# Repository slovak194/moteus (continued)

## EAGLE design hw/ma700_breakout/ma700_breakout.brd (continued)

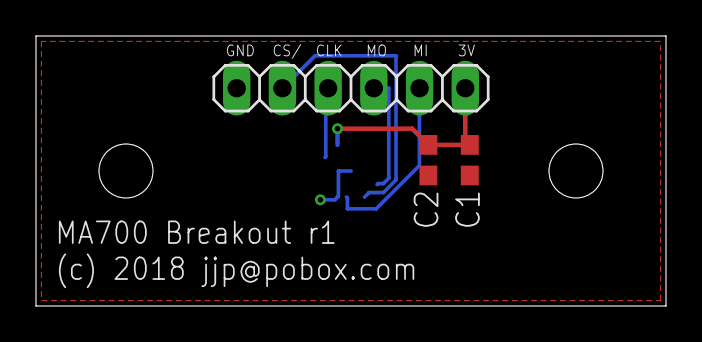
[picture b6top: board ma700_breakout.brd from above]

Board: 2 copper layers, 35.0 x 15.0 mm, 4 parts (1 on the bottom side), 6 nets.

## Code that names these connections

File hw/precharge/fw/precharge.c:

// Copyright 2019 Josh Pieper, jjp@pobox.com.
//
// Licensed under the Apache License, Version 2.0 (the "License");
// you may not use this file except in compliance with the License.
// You may obtain a copy of the License at
//
//     http://www.apache.org/licenses/LICENSE-2.0
//
// Unless required by applicable law or agreed to in writing, software
// distributed under the License is distributed on an "AS IS" BASIS,
// WITHOUT WARRANTIES OR CONDITIONS OF ANY KIND, either express or implied.
// See the License for the specific language governing permissions and
// limitations under the License.

#include <avr/cpufunc.h>
#include <avr/interrupt.h>
#include <avr/io.h>
#include <util/delay.h>

//                 --------------
//               --|VCC      GND|--
//    FET_MAIN   --|PB0      PA0|-- VSAMP_IN
//    FET_PCHG   --|PB1      PA1|-- VSAMP_OUT
//       RESET   --|PB3      PA2|-- LED1
//               --|PB2      PA3|-- LED2
//               --|PA7      PA4|-- SCK
//       MOSI    --|PA6      PA5|-- MISO
//                 --------------

#define LED1 0x04
#define LED2 0x08

#define FET_MAIN 0x01
#define FET_PCHG 0x02

int main() {
  // We leave the clock at the original 1MHz, because this application
  // really does not need high speed.

  // Disable digital inputs on our sense lines.
  DIDR0 =
      (1 << ADC1D) |
      (1 << ADC0D);

  // Set our LEDs for output.
  PORTA |= (LED1 | LED2);
  DDRA = (LED1 | LED2);

  PORTB = 0x00;
  DDRB = (FET_MAIN | FET_PCHG);

  _delay_ms(10);
  PORTB |= FET_PCHG;

  _delay_ms(100);
  PORTB |= FET_MAIN;

  for (;;) {
    PORTA |= LED1;
    _delay_ms(970);
    PORTA &= ~LED1;
    _delay_ms(30);
  }

  return 0;
}

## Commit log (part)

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2019-09-19 Fix a sign warning
2019-09-20 ProgramOptionsArchive: Ignore vectors for now
2019-09-24 Remove stale comment
2019-09-27 Work on r4 of controller
    Parts are in place, but part names are bogus, silks haven't been
    placed, and auto-routing not done yet.
2019-09-27 All silks rough placed and all part numbers fixed up
2019-09-28 Nearly final version
    Still need to verify the footprints of all the JST connectors
2019-09-30 Add some more ground debug pins
2019-09-30 power dist: Fix some silks and MPNs found by macrofab
2019-10-01 Switch to actually using the SOT23-8 variant of the TCAN334G
2019-10-03 Power distribution r1 as sent to macrofab
2019-10-03 Mark some more things as not populated
2019-10-03 Make the openocd scripts work for more openocd versions
2019-10-03 When in the PositionTimeout state, also zero feedforward torque and velocity
2019-10-10 Updates to chassis v2
2019-10-16 More power dist errata:
    * Fix 10k resistors
    * Rename TCAN package to actually be SOIC8, since that is what it is
2019-10-16 More random leg parts
2019-10-16 power dist r2 as sent to mf
2019-10-16 Report 0 torque when the sense amplifiers aren't on and calibrated
2019-10-24 Add a non-latching zero velocity mode
2019-10-28 Implement flux braking
    This acts as a virtual resistor when the bus voltage is too high.
    Instead of a brake chopper, it lets you just dump extra heat into the
    motors.
2019-11-01 Rename precharge to power_dist
2019-11-03 chassis v2 errata
2019-11-03 Beginnings of power_dist firmware
2019-11-04 controller: Tweak a silk position
2019-11-04 controller: Actually use a 2k resistor for I2C pullup
2019-11-04 controller: Sigh, I managed to tweak that silk onto a pad
2019-11-07 Update TODOs
2019-11-07 Remove v1 chassis, v2 is done and working
2019-11-07 This breakout will never be used
2019-11-07 No one needs the insert test
2019-11-07 controller r4.1 as sent to macrofab
2019-11-12 Various fixtures
2019-11-22 Remove the "smart" imu_junction board firmware
    It will never be used.
2019-11-24 Update to a rules_mbed that doesn't modify the input args to mbed_binary
2019-11-24 Stub out non-functional support for a stm32g4 based controller
2019-11-30 Switch to use AtomicEventQueue from mjlib
2019-12-01 We should never have left this uninitialized
2019-12-04 Further work towards r4.1 support
    * Incorporate the uart driver from fdcanusb
    * rename all the part specific things so that g4 is unadorned
2019-12-05 Actually work
2019-12-05 Make device signature work on stm32g4
2019-12-05 Oops, forgot to give a string for this error
2019-12-05 Update various TODOs
2019-12-06 r3.1 as sent to MacroFab
2019-12-06 Use the correct debug UART pin on each board type
2019-12-06 Drop the drv8323 frequency a bit lower still
2019-12-06 We're not dual sampling anymore in r4.1, so just use the right currents
2019-12-06 Only use 115200 for uart on g4 for now
2019-12-06 Update rules_mbed to one with a properly aligned stack for stm32g4
2019-12-06 Fix comments in linker script
2019-12-06 Change default gear ratio to 1/6, since that is what every servo I've got uses
2019-12-06 py_moteus_tool: Calibrate successfully even at 115200
2019-12-06 Switch to a mjlib::multiplex::MicroServer that supports alternate transports
2019-12-07 Implement FDCAN based MicroServer
2019-12-08 py_moteus_tool: Add hacky hacky fdcanusb support
2019-12-09 Get control loop running at correct rate on stm32g4
    This probably also fixes it on the stm32f4 as well. While we are at
    it, use the correct debug pins on the r4.1 board.
2019-12-09 Move everything feasible from the hot-loop to CCM
    To accomplish this, fork the mjlib PID, as there is no easy way to
    assign symbols or external libraries into CCM.
    This gets the ISR time down to 14.2us
2019-12-09 Use 40kHz rate on r4.1
2019-12-09 Expose the D current on DAC1 for debugging
2019-12-09 Note a minor r4.1 silk nit
2019-12-16 Remove stale debug print
2019-12-16 Slightly increase the time for current sampling
2019-12-16 Brackets for mk2 outer housing
2019-12-16 Minor tweaks for a r4.2 moteus controller
    * Add two pullups
    * Tweak some silk
    * Update the version number on board and schematic
2019-12-25 Add the unmodified tview main window UI file from mjbots/mjmech
2019-12-30 Update mjlib
    This updates moteus_tool to use clipp and the new Selector API
2019-12-30 Tweak moteus_tool signature to support external selectors
2020-01-06 Update moteus_tool to use coroutines
    This also upgrades mjlib so that we have fdcanusb support. rs485
    support is current untested in this version, particularly flashing, so
    it is more of a checkpoint.
2020-01-09 Make tview actually work with the new telemetry format
2020-01-10 Correctly set the flash option
2020-01-11 Tweak the default current control kp for less audible noise
2020-01-11 Implement calibration in C++ moteus tool
2020-01-14 Remove unused tab in tview
2020-01-14 moteus_tool: Check for faults during calibration
2020-01-14 Add a r4.2 errata
2020-01-14 moteus_tool: More calibration improvements * Make kv determination more robust * Always store the results to disk, trying a few directories before falling back to cwd
2020-01-15 Updates to README
2020-01-15 Add mechanical pdf and pinouts to README
2020-01-15 moteus_tool: Record and report the git hash when calibrating
2020-01-16 Nominally complete, but highly unlikely to actually work can bootloader
2020-01-16 Fix enough in the CAN bootloader so that basic stream comms works
2020-01-17 Fix enough bugs in the g4 bootloader that I was able to flash things!
2020-01-17 Build multiplex_tool in the moteus repository
2020-01-17 Implement temperature derating
    Also, artifically limit the maximum current to 60A and configure the
    voltage and flux braking for the r4.2 controllers maximum limits.
2020-01-20 Magnet adapter for devkit
2020-01-20 Make velocity filter configurable in length
    This requires updating mjlib
2020-01-20 Update BUILD with current bootloader targets
2020-01-21 moteus_tool: Support printing out device info
2020-01-21 Don't drop lines if multiple are pulled into the streambuf at once
2020-01-22 Add a config for the beta devkit
2020-01-24 Slightly tweak openocd build steps
2020-01-30 Beginnings of mk2 leg
2020-01-31 Correct digikey number for battery terminal
2020-02-03 Random leg hardware
2020-02-11 Rename gearbox_v2 to mk2_servo
2020-02-11 Beginning of a BOM for the chassis
2020-02-12 Beginnings of bom for mk2 servo
2020-02-12 Update servo TODO
2020-02-12 Current casting procedure
2020-02-13 An array of magnet holders
2020-02-13 Add the mjbots logo
2020-02-14 Updated lower leg 3dprint
2020-02-14 More work on mk2 servo bom and assembly
2020-02-16 Give log poly an actual width
2020-02-22 Switch plate stl
2020-02-24 Ensure moteus_tool is built by //:host
2020-02-24 Updated shoulder and upper motor joint
2020-02-27 To let the host send lots of queries at once, we need auto retransmission
2020-02-27 moteus_tool: Support rezeroing the motor
2020-02-29 Update FDCan to match that in fdcanusb
2020-02-29 Add mjbots logo to power dist board
2020-02-29 r3 of power dist as sent for mfg
2020-03-01 Reword dependencies to be clearer about what you need which things for
2020-03-01 Draft of a register based communication example
2020-03-03 New bottom plates and battery stud
2020-03-05 moteus_tool: We likely won't receive the response to a "reset" command
2020-03-13 3d prints for qdd100 devkit
2020-03-15 Add mechanical drawing of qdd100
2020-03-15 Lower max current back down to 65A.
2020-03-16 Update the reference documentation to be self contained
    This duplicates the minimal set of multiplex protocol and register
    mappings to be able to put the device into position mode.
2020-03-19 tview: Add a hacky way to plot stddev and mean
2020-03-20 Update to a newer rules_mbed and enable speed optimization
2020-03-20 Switch voltage int8 mapping to be 0.5V
    We're already revising the register map version. Since we're unlikely
    to ever have voltages more than 64V for the foreseeable future, get
    some extra resolution in the int8 version of voltages.
2020-03-20 Add a DQ voltage mode
    This makes calibrating the Kv constant much easier.
    It also necessitates reving the register map version.
2020-03-20 Switch to checking for isnan for validity instead of isfinite
    This allows the position limit to be entirely disabled by setting NaN
    without the non-intuitive behavior of infinity resulting in it being
    disabled. Apply the same logic to everything else that could be
    disabled with non-finite values.
2020-03-20 Interleave the sampling of the AS5047 with other work
    There unfortunately isn't a lot it can be interleaved with, but this
    does save about 100 cycles off the total ISR time.
2020-04-08 r4.4 changes minus autorouting
2020-04-10 Tweak some silks and traces
2020-04-11 Document why(?) we are inverting the order of stepping
2020-04-12 More silk and layout tweaks
2020-04-23 Some stls for the new chassis
2020-04-23 A fixture for assembling planet inputs
2020-04-23 Switch capacitors to soft termination variant
    Round corners
2020-04-23 r3.1 as sent to mfg
2020-04-28 Magnet holders
2020-04-28 moteus_tool: Support configurable voltages for calibration
2020-04-28 Actually make -Werror work
2020-05-02 Add some leg todos
2020-05-02 Leg zeroing fixtures
2020-05-02 Tweak down the wire length
2020-05-11 Various pieces of hardware
2020-05-11 Fault if started outside of the position limit
2020-05-25 Add a link to the chassis CAD
2020-06-02 By default, capture and restore config across flash
    Since the controller doesn't perform any schema mapping when loading
    configs, if the schema for any configuration changed, it would be lost
    after re-flashing. We now capture everything as text, then command it
    back after the flash so that it all is persisted.
    A cmdline flag (--no-restore-config) can disable this behavior.
2020-06-05 Include the git hash in the power dist firmware
    It isn't used anywhere here yet, but allows the provisioning tool to
    extract it from the elf.
2020-06-14 Slightly tweak mk2 leg assembly instructions and add more fixtures
2020-06-19 Increase the maximum achievable velocity by a factor of 256
    Previously, we were limited to roughly 77Hz before the velocity filter
    would have something inserted that overflowed a uint16. Now we do the
    averaging in the floating point domain, which removes that limitation
    on maximum velocity. Things which still limit velocity:
    * The kv of the motor and the maximum supply voltage
    * The 466Hz limitation of the AS5047 encoder
2020-06-24 Fix path in calibration doc
2020-06-27 Updated leg
2020-07-08 Minor bom update, about to be removed anyhow
2020-07-08 Print 2 foot brackets with each lower leg
    Foaming the feet has a moderate failure rate, this will ensure enough
    brackets are around to account for loss.
2020-07-08 Enable supports for the chassis sides
2020-07-08 All uses of 'conf enumerate' need a longer timeout
2020-07-27 Update qdd100 TODO and add a 3d printed spacer
2020-07-27 Uprate the moteus to 100A based on bench testing
2020-07-28 Specify the test sizes to be small
2020-07-28 We need to apply the torque model pre-gearbox
2020-07-28 Report the correct Kv rating of the motor
    This is purely cosmetic. The v_per_hz was correct, and the torque
    constant needs a fudge to maintain the correct torque, but now at
    least the reported Kv matches wikipedia and what the mfg's report.
2020-07-28 Upgrade to clang 10
2020-07-28 The SPI class is actually generic to all the STM32s we support
2020-07-30 A simple adapter to fit an ma732 in place of the as5047
2020-07-30 More size tweaks
2020-08-02 Decrease default PID gains
2020-08-09 Add a simple paddle for the qdd100
2020-08-09 Support the r4.4 board with the same fw image as the r4.3 board
    While we are at it, actually sample all 3 current phases, even though
    we still only use two of them to calculate the D/Q currents.
2020-08-10 Remove all code for F4 based boards
2020-08-10 Add a test for WrapZeroToTwoPi
2020-08-10 Minor improvements to the FOC math
    * Use CORDIC for more accurate sine/cosine
    * Do electrical theta wrapping in integer coordinate space
    This doesn't seem to affect any visible performance results, but are
    all "good" things to have.
    Use the CORDIC for more accurate floating point
2020-08-11 Improve current sense noise
    * Assign current sense pins to all "slow" channels, so they'll be
    treated the same
    * Set sampling time to 24 cycles for current
    * Reorder when ADC channels are started for unknown reasons, but it
    does make things better
    * Stop fiddling with debug GPIOs until after the current sampling is over
